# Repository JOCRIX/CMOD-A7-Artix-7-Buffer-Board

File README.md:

# **Buffer Board for the CMOD A7 Artix 7 family of FPGA development boards**

## **Purpose of the project**
The development boards for these FPGA's are costly and, sadly, a little fumbling around
could easily claim it's life, so, the purpose of this project is to create a board that can buffer the I/O pins
on the Digilent CMOD A7 FPGA board. (Mfr: 410-328-35, Mouser.com nr:424-410-328-35).

All design files are for KiCad. Feel free to export the GERBERS and do w/e with it.

## **How it works**
The board uses TXB0108 bidirectional and auto-direction sensing buffers to buffer all the I/O pins. The buffers
do not require any signal to set them as inputs or outputs, this is handled automatically on the fly. Each pin
has a maximum I/O current of 50mA and a package total of 100mA per buffer IC. The purpose of the board is 
that the drivers will fail before the FPGA does, that is OK. The FPGA is connected to the buffers through
330 ohm resistors, so, if the buffers fail in a spectacular way the FPGA output current is limited to stay
within specification of the Artix 7 35T FPGA.

The rise and fall times of the output of the buffer board has been tested and both rise and fall times are 4 < t < 5 [nS].

The two ADC input pins AIN/NP15, AIN/NP16 are protected against overvoltage conditions with diodes.

## **Requirements / BOM**

1x CMOD A7 FPGA Board - https://www.mouser.dk/ProductDetail/Digilent/410-328-35?qs=iHX4uCgIbgPRh1v3D3f51A%3D%3D
<br>
6x TXB0108 [TSSOP20]
<br>
11x YC324, or similar, 330 ohm resistor array.
<br>
2x 24 Pin Female headers with 2.54mm pitch
<br>
2x 24 Pin Female/Male header with 2.54mm pitch
<br>
1x LD117S533TR [SOT223]
<br>
7x 100nF >6.3V [0805]
<br>
1x 0603 LED (Doesn't really matter but it looks cool!)
<br>
1x 560R [0805]
<br>
1x 10uF [0805]
<br>
4x BAT54 [SOD-123]

## Hope you like Warhammer..

### Notes for users
V1 of this board has a fault so **PIO26 [FPGA PIN: R3] is not connected**. This is to be fixed in a future revision.
The problem can be fixed with a jumper wire for now. (Or just edit the .sch but w/e :)).

The green trace shows the connection that should be made for R3 to work. Easily fixed in either case..

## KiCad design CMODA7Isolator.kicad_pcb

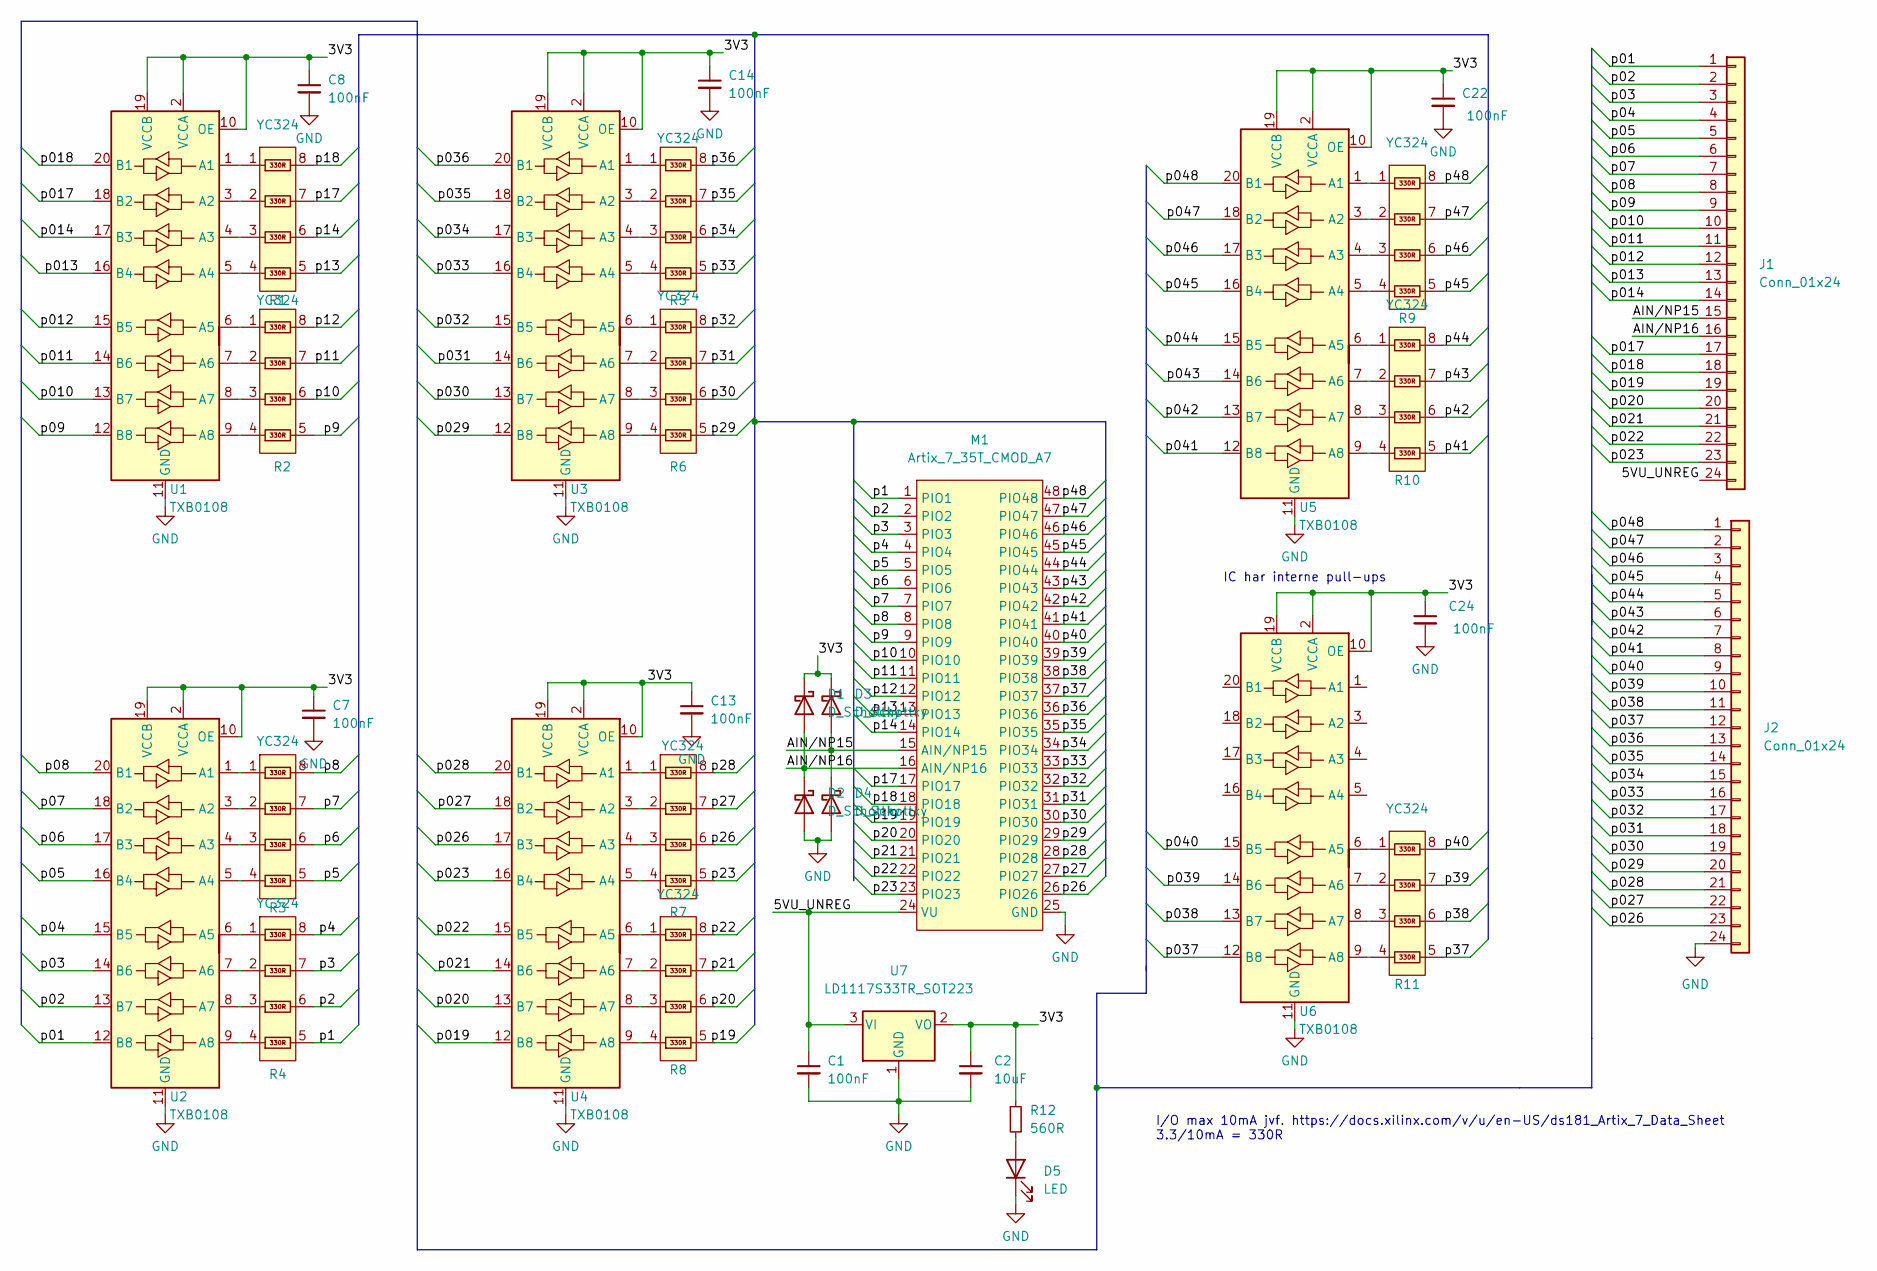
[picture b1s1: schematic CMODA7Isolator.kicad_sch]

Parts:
C1, C7, C8, C13, C14, C22, C24: 100nF; C_0805_2012Metric_Pad1.18x1.45mm_HandSolder
C2: 10uF; C_0805_2012Metric_Pad1.18x1.45mm_HandSolder
D1, D2, D3, D4: D_Schottky; D_SOD-123
D5: LED; LED_0603_1608Metric
J1, J2: Conn_01x24; PinHeader_1x24_P2.54mm_Vertical
M1: Artix_7_35T_CMOD_A7; CMOD A7 Module
R1, R2, R3, R4, R5, R6, R7, R8, R9, R10, R11: YC324; YC-TC 124 8Pin-4R
R12: 560R; R_0805_2012Metric_Pad1.20x1.40mm_HandSolder
U1, U2, U3, U4, U5, U6: TXB0108; TSSOP-20_4.4x6.5mm_P0.65mm
U7: LD1117S33TR_SOT223; SOT-223-3_TabPin2

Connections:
/3V3: C2.1, C7.1, C8.1, C13.1, C14.1, C22.1, C24.1, D1.1 (K), D3.1 (K), R12.1, U1.2 (VCCA), U1.10 (OE), U1.19 (VCCB), U2.2 (VCCA), U2.10 (OE), U2.19 (VCCB), U3.2 (VCCA), U3.10 (OE), U3.19 (VCCB), U4.2 (VCCA), U4.10 (OE), U4.19 (VCCB), U5.2 (VCCA), U5.10 (OE), U5.19 (VCCB), U6.2 (VCCA), U6.10 (OE), U6.19 (VCCB), U7.2 (VO)
/5VU_UNREG: C1.1, J1.24, M1.24 (VU), U7.3 (VI)
/AIN/NP15: D3.2 (A), D4.1 (K), J1.15, M1.15 (AIN/NP15)
/AIN/NP16: D1.2 (A), D2.1 (K), J1.16, M1.16 (AIN/NP16)
/p01: J1.1, U2.12 (B8)
/p1: M1.1 (PIO1), R4.5
/p02: J1.2, U2.13 (B7)
/p2: M1.2 (PIO2), R4.6
/p03: J1.3, U2.14 (B6)
/p3: M1.3 (PIO3), R4.7
/p04: J1.4, U2.15 (B5)
/p4: M1.4 (PIO4), R4.8
/p5: M1.5 (PIO5), R3.5
/p05: J1.5, U2.16 (B4)
/p6: M1.6 (PIO6), R3.6
/p06: J1.6, U2.17 (B3)
/p7: M1.7 (PIO7), R3.7
/p07: J1.7, U2.18 (B2)
/p8: M1.8 (PIO8), R3.8
/p08: J1.8, U2.20 (B1)
/p09: J1.9, U1.12 (B8)
/p9: M1.9 (PIO9), R2.5
/p010: J1.10, U1.13 (B7)
/p10: M1.10 (PIO10), R2.6
/p011: J1.11, U1.14 (B6)
/p11: M1.11 (PIO11), R2.7
/p012: J1.12, U1.15 (B5)
/p12: M1.12 (PIO12), R2.8
/p013: J1.13, U1.16 (B4)
/p13: M1.13 (PIO13), R1.5
/p014: J1.14, U1.17 (B3)
/p14: M1.14 (PIO14), R1.6
/p017: J1.17, U1.18 (B2)
/p17: M1.17 (PIO17), R1.7
/p018: J1.18, U1.20 (B1)
/p18: M1.18 (PIO18), R1.8
/p19: M1.19 (PIO19), R8.5
/p019: J1.19, U4.12 (B8)
/p20: M1.20 (PIO20), R8.6
/p020: J1.20, U4.13 (B7)
/p21: M1.21 (PIO21), R8.7
/p021: J1.21, U4.14 (B6)
/p22: M1.22 (PIO22), R8.8
/p022: J1.22, U4.15 (B5)
/p23: M1.23 (PIO23), R7.5
/p023: J1.23, U4.16 (B4)
/p26: M1.26 (PIO26), R7.6
/p026: J2.23, U4.17 (B3)
/p27: M1.27 (PIO27), R7.7
/p027: J2.22, U4.18 (B2)
/p28: M1.28 (PIO28), R7.8
/p028: J2.21, U4.20 (B1)
/p29: M1.29 (PIO29), R6.5
/p029: J2.20, U3.12 (B8)
/p30: M1.30 (PIO30), R6.6
/p030: J2.19, U3.13 (B7)
/p31: M1.31 (PIO31), R6.7
/p031: J2.18, U3.14 (B6)
/p32: M1.32 (PIO32), R6.8
/p032: J2.17, U3.15 (B5)
/p33: M1.33 (PIO33), R5.5
/p033: J2.16, U3.16 (B4)
/p34: M1.34 (PIO34), R5.6
/p034: J2.15, U3.17 (B3)
/p35: M1.35 (PIO35), R5.7
/p035: J2.14, U3.18 (B2)
/p36: M1.36 (PIO36), R5.8
/p036: J2.13, U3.20 (B1)
/p37: M1.37 (PIO37), R11.5
/p037: J2.12, U6.12 (B8)
/p38: M1.38 (PIO38), R11.6
/p038: J2.11, U6.13 (B7)
/p39: M1.39 (PIO39), R11.7
/p039: J2.10, U6.14 (B6)
/p40: M1.40 (PIO40), R11.8
/p040: J2.9, U6.15 (B5)
/p41: M1.41 (PIO41), R10.5
/p041: J2.8, U5.12 (B8)
/p42: M1.42 (PIO42), R10.6
/p042: J2.7, U5.13 (B7)
/p43: M1.43 (PIO43), R10.7
/p043: J2.6, U5.14 (B6)
/p44: M1.44 (PIO44), R10.8
/p044: J2.5, U5.15 (B5)
/p45: M1.45 (PIO45), R9.5
/p045: J2.4, U5.16 (B4)
/p46: M1.46 (PIO46), R9.6
/p046: J2.3, U5.17 (B3)
/p47: M1.47 (PIO47), R9.7
/p047: J2.2, U5.18 (B2)
/p48: M1.48 (PIO48), R9.8
/p048: J2.1, U5.20 (B1)
GND: C1.2, C2.2, C7.2, C8.2, C13.2, C14.2, C22.2, C24.2, D2.2 (A), D4.2 (A), D5.1 (K), J2.24, M1.25 (GND), U1.11 (GND), U2.11 (GND), U3.11 (GND), U4.11 (GND), U5.11 (GND), U6.11 (GND), U7.1 (GND)
unnamed: D5.2 (A), R12.2
unnamed: R1.1, U1.1 (A1)
unnamed: R1.2, U1.3 (A2)
unnamed: R1.3, U1.4 (A3)
unnamed: R1.4, U1.5 (A4)
unnamed: R2.1, U1.6 (A5)
unnamed: R2.2, U1.7 (A6)
unnamed: R2.3, U1.8 (A7)
unnamed: R2.4, U1.9 (A8)
unnamed: R3.1, U2.1 (A1)
unnamed: R3.2, U2.3 (A2)
unnamed: R3.3, U2.4 (A3)
unnamed: R3.4, U2.5 (A4)
unnamed: R4.1, U2.6 (A5)
unnamed: R4.2, U2.7 (A6)
unnamed: R4.3, U2.8 (A7)
unnamed: R4.4, U2.9 (A8)
unnamed: R5.1, U3.1 (A1)
unnamed: R5.2, U3.3 (A2)
unnamed: R5.3, U3.4 (A3)
unnamed: R5.4, U3.5 (A4)
unnamed: R6.1, U3.6 (A5)
unnamed: R6.2, U3.7 (A6)
unnamed: R6.3, U3.8 (A7)
unnamed: R6.4, U3.9 (A8)
unnamed: R7.1, U4.1 (A1)
unnamed: R7.2, U4.3 (A2)
unnamed: R7.3, U4.4 (A3)
unnamed: R7.4, U4.5 (A4)
unnamed: R8.1, U4.6 (A5)
unnamed: R8.2, U4.7 (A6)
unnamed: R8.3, U4.8 (A7)
unnamed: R8.4, U4.9 (A8)
unnamed: R9.1, U5.1 (A1)
unnamed: R9.2, U5.3 (A2)
unnamed: R9.3, U5.4 (A3)
unnamed: R9.4, U5.5 (A4)
unnamed: R10.1, U5.6 (A5)
unnamed: R10.2, U5.7 (A6)
unnamed: R10.3, U5.8 (A7)
unnamed: R10.4, U5.9 (A8)
unnamed: R11.1, U6.6 (A5)
unnamed: R11.2, U6.7 (A6)
unnamed: R11.3, U6.8 (A7)
unnamed: R11.4, U6.9 (A8)

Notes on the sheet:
I/O max 10mA jvf. https://docs.xilinx.com/v/u/en-US/ds181_Artix_7_Data_Sheet 3.3/10mA = 330R
IC har interne pull-ups

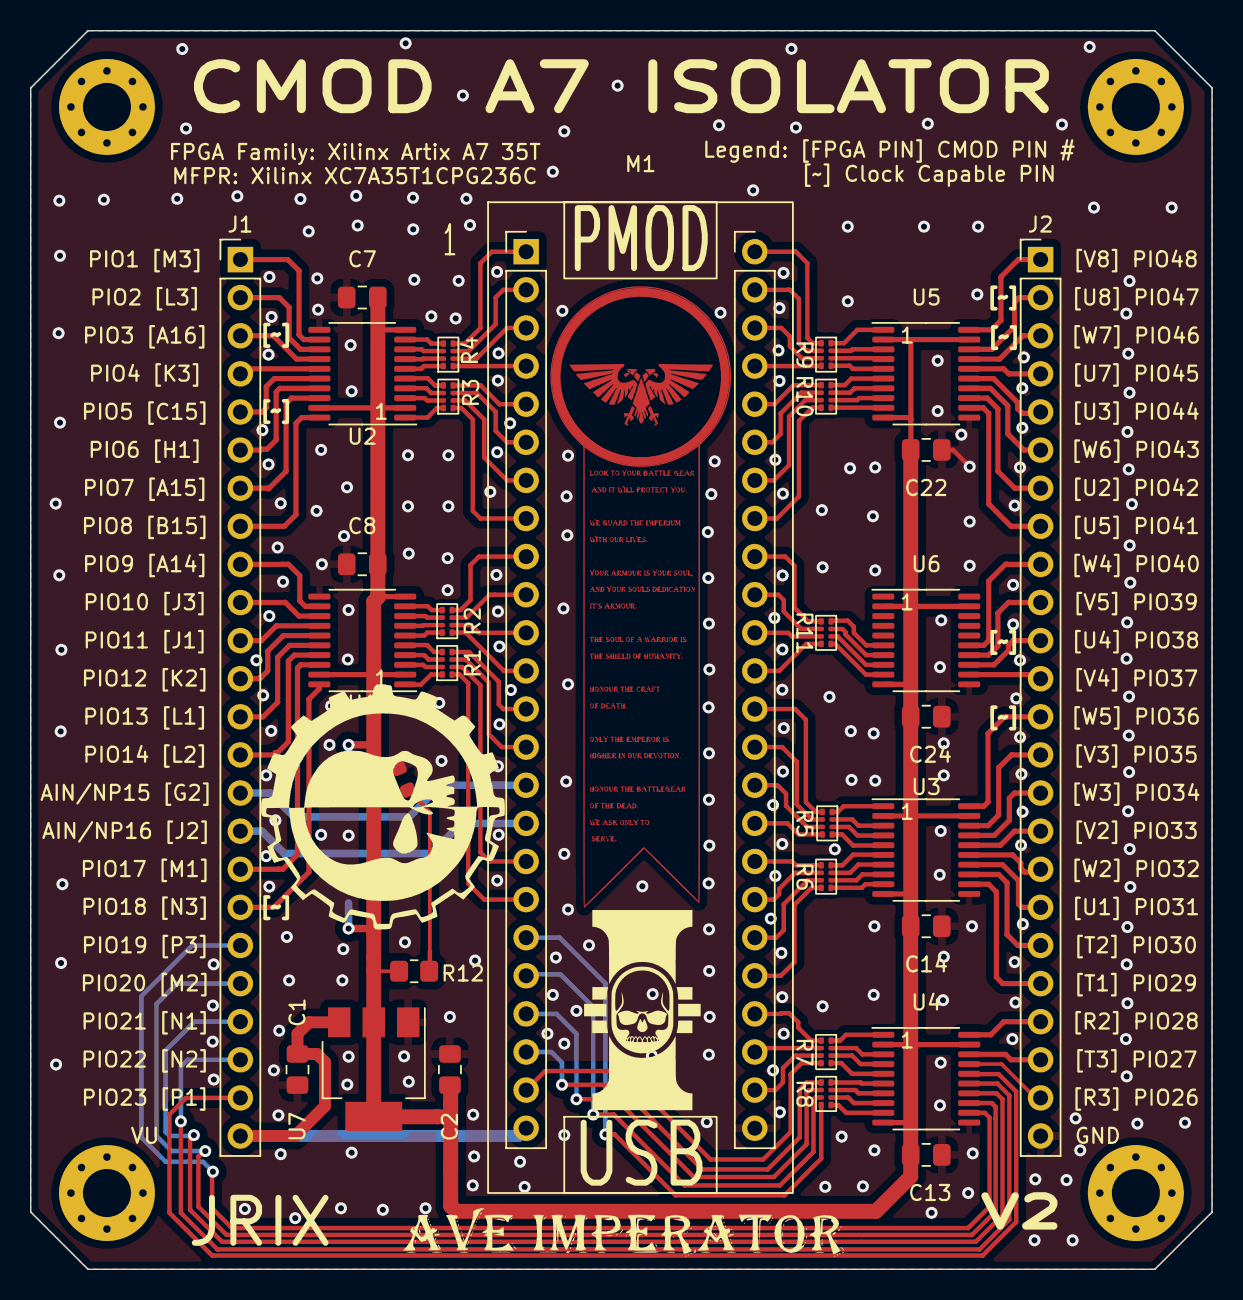
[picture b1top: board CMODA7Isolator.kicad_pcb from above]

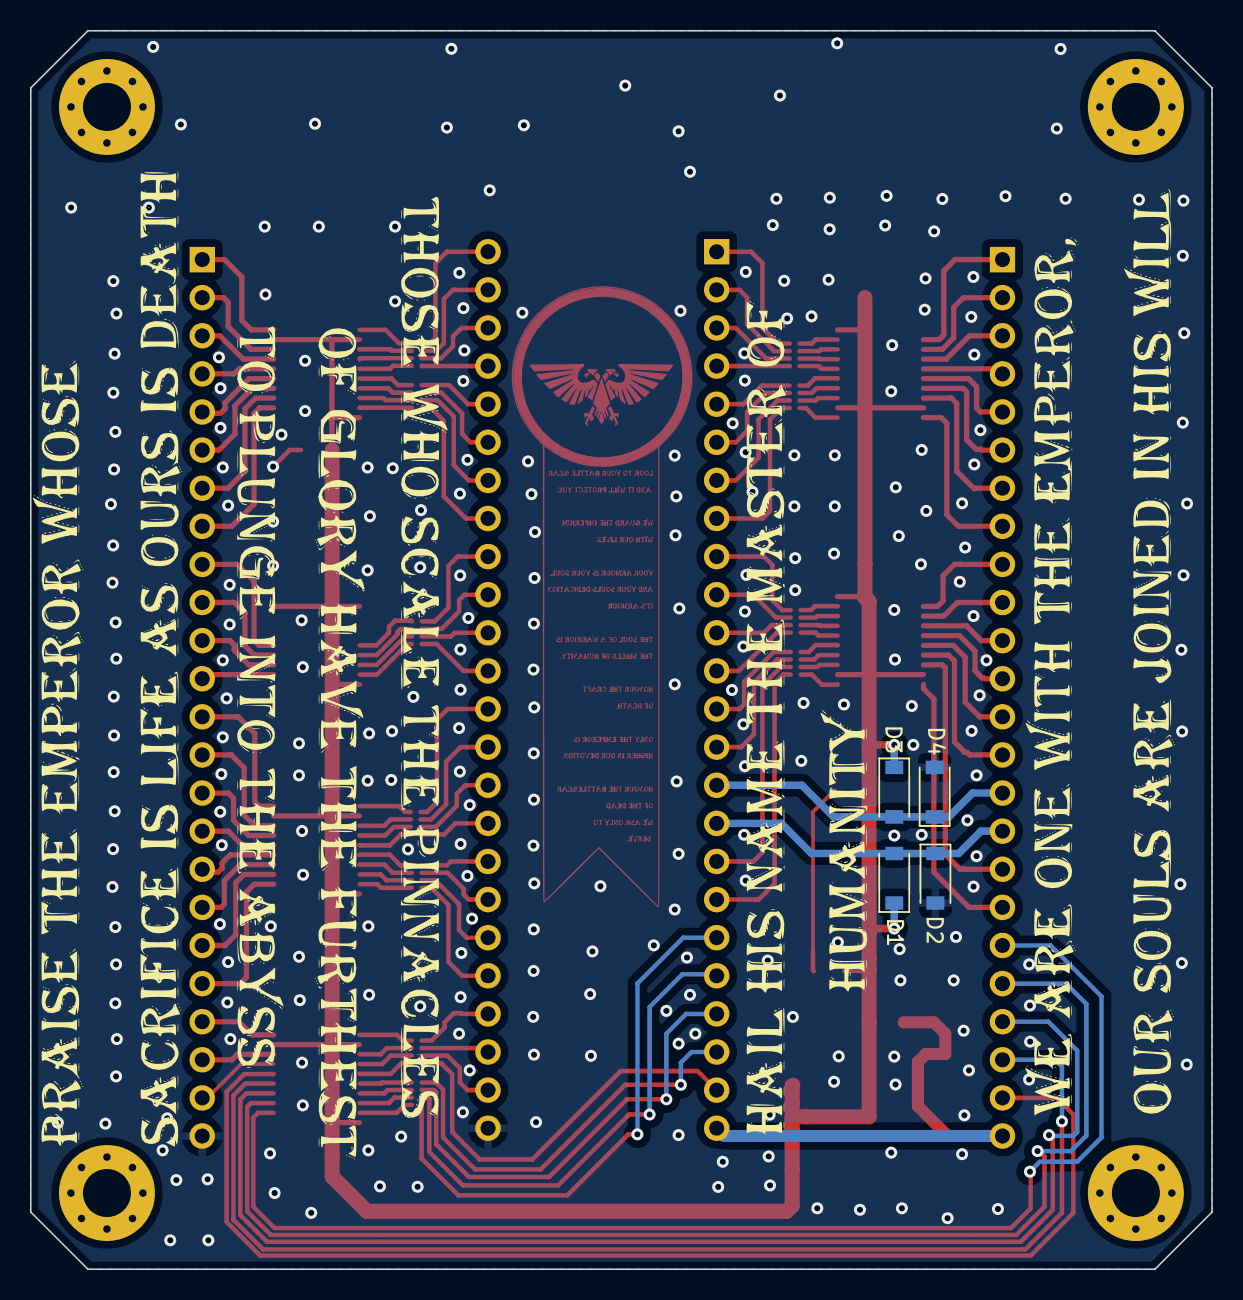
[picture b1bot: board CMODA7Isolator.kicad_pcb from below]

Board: 2 copper layers, 78.7 x 82.6 mm, 35 parts (4 on the bottom side), 138 nets.

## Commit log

2023-03-10 Initial release of all documentation for the CMOD A7 Buffer board
2023-03-10 Removed some junk files
2023-03-10 Added images for readme
2023-03-10 Updated readme with image links
2023-03-11 Test branch feature and added IO Standard sheet for V2 development
2023-03-11 Test of branching
2023-03-11 Fixed Issue #3
2023-03-11 Issue #1 work done, needs testing to verify..
2023-03-11 Issue #6 fixed
2023-03-11 Fixed issue #4 added more power pins
2023-03-11 Issue #5 and issue #6 fixed in schematic. Comprehensive PCB update required.
2023-03-12 PCB work 12/3
2023-03-12 added missing footprints
